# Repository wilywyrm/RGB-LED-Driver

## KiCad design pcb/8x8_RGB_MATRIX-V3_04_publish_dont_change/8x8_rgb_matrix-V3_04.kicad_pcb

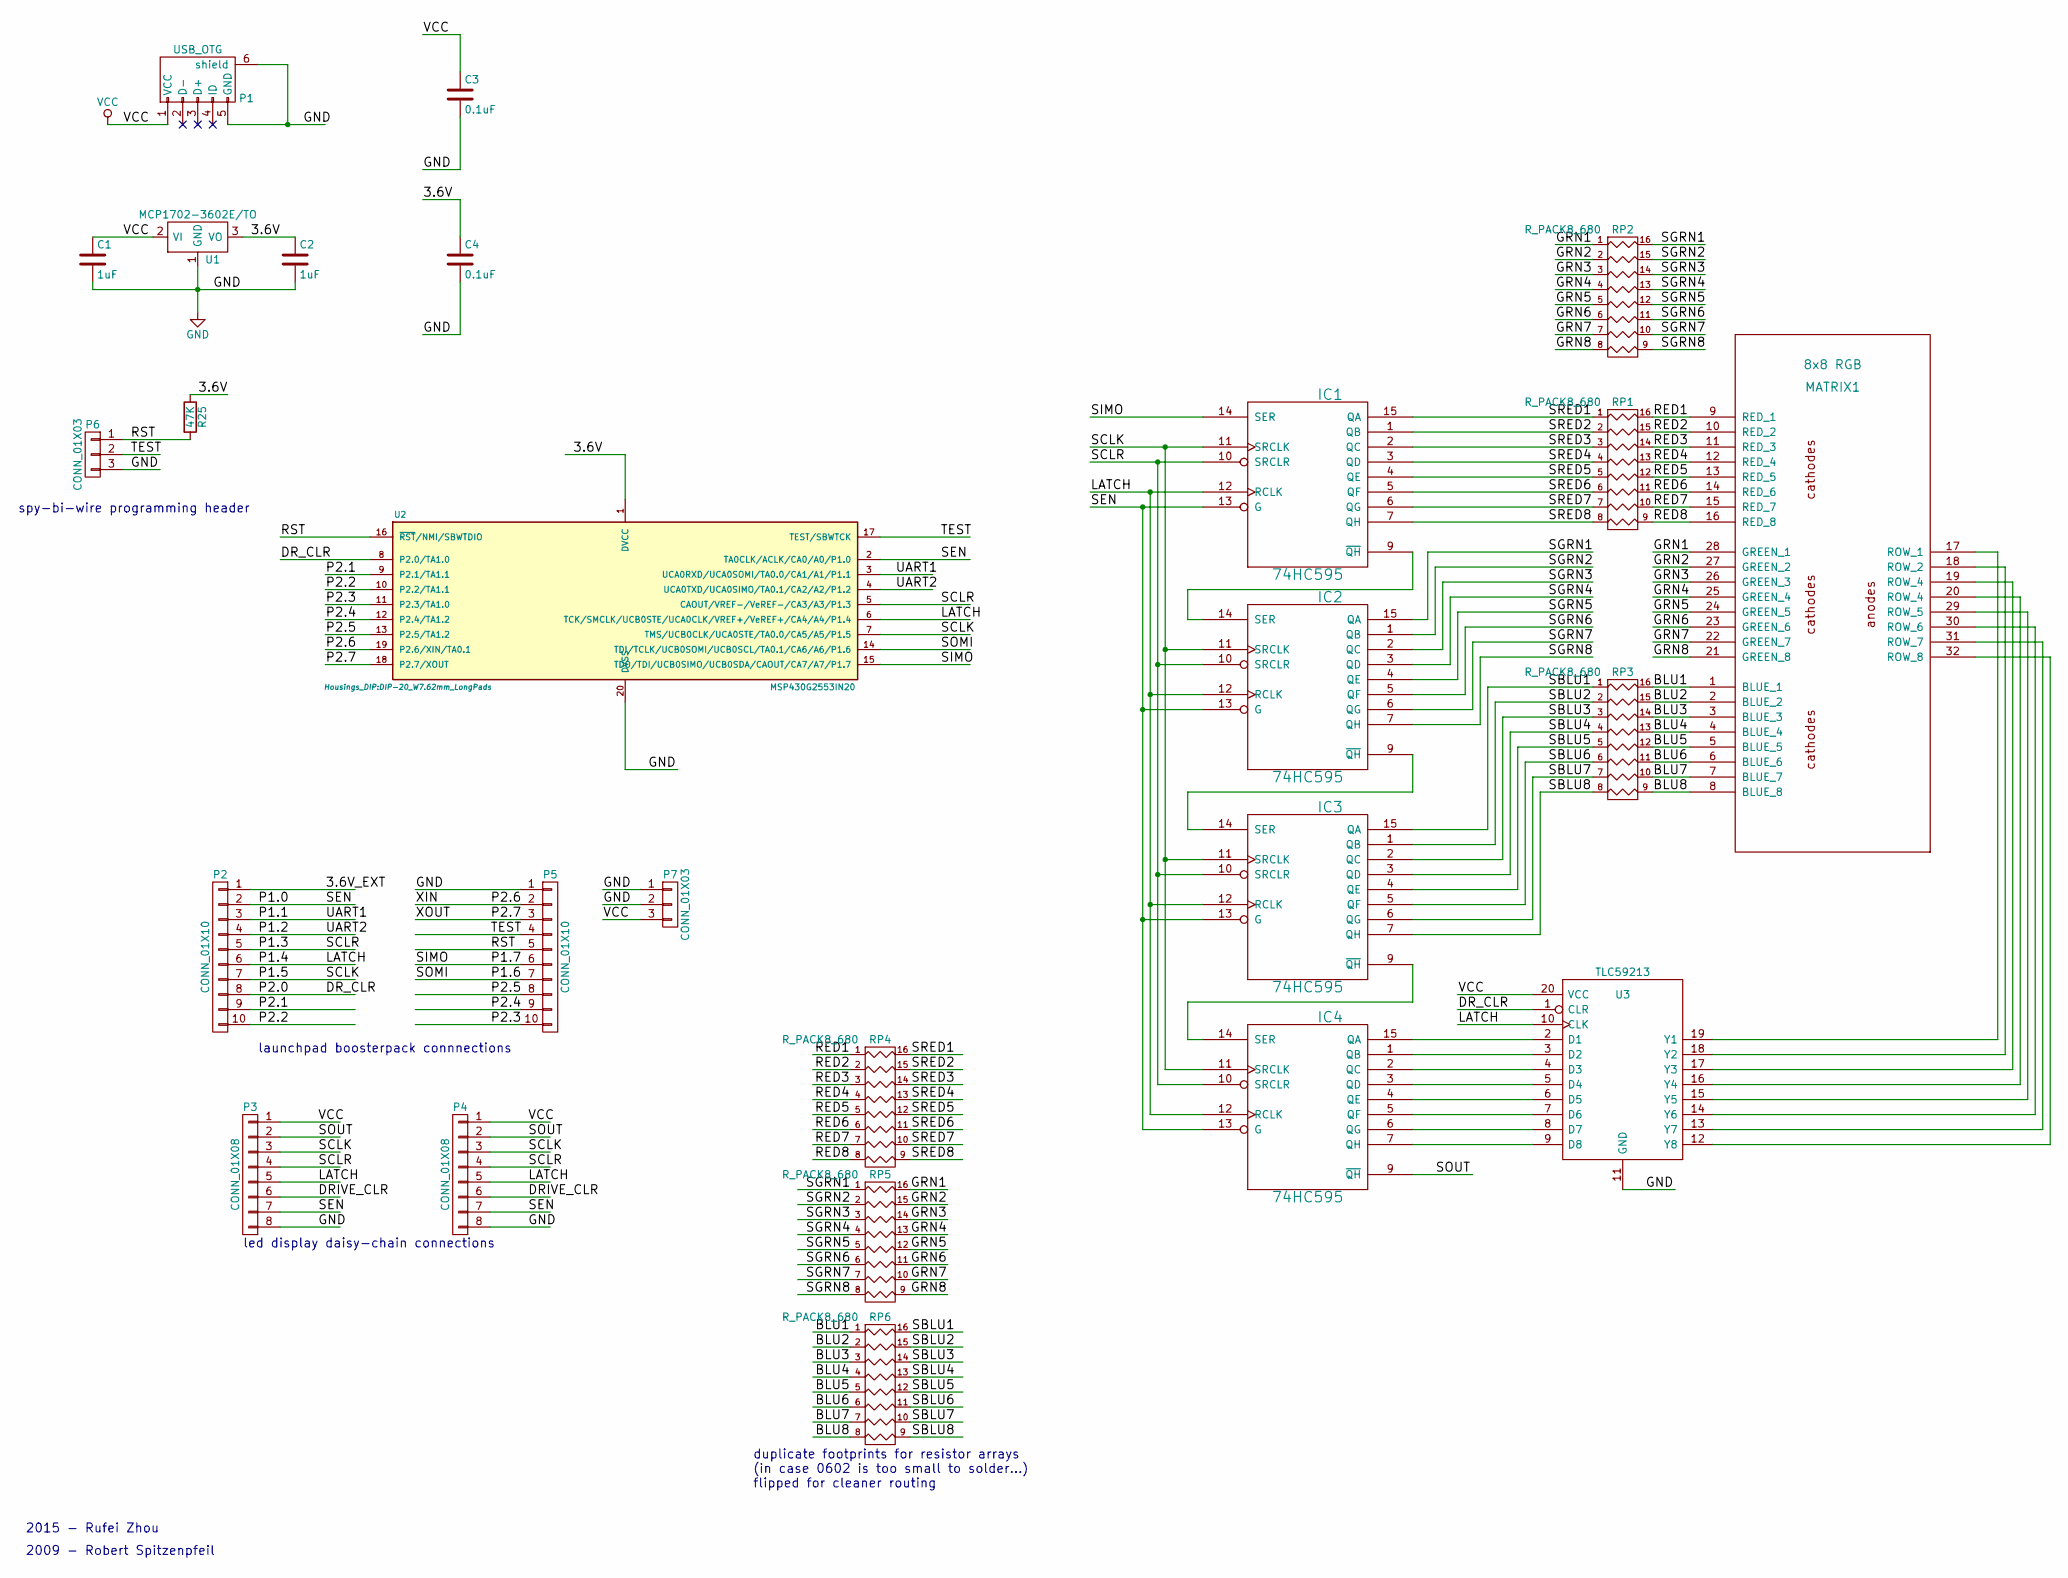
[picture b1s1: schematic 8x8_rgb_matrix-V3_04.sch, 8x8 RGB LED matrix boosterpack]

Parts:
C1, C2: 1uF; C_Disc_D3_P2.5
C3, C4: 0.1uF; C_Disc_D3_P2.5
IC1, IC2, IC3, IC4: 74HC595; SOIC-16_3.9x9.9mm_Pitch1.27mm
MATRIX1: 8x8 RGB; MADW__LEDSEE_8x8_RGB
P1: USB_OTG; USB_Micro-B_FCI
P2, P5: CONN_01X10; Pin_Header_Straight_1x10
P3: CONN_01X08; Pin_Header_Angled_1x08
P4: CONN_01X08; Pin_Header_Straight_1x08
P6, P7: CONN_01X03; Pin_Header_Straight_1x03
R25: 47K; R3
RP1, RP2, RP3: R_PACK8_680; R_Array_Convex_8x0602
RP4, RP5, RP6: R_PACK8_680; R_Array_Convex_8_2406
U1: MCP1702-3602E/TO; TO-92_Inline_Narrow_Oval
U2: MSP430G2553IN20; DIP-20_W7.62mm_LongPads
U3: TLC59213; DIP-20_W7.62mm_LongPads

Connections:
/3.6V: C2.1, C4.1, R25.1, U1.3 (VO), U2.1 (DVCC)
/3.6V_EXT: P2.1
/BLU1: MATRIX1.1 (BLUE_1), RP3.16 (R1), RP6.1; also elsewhere on the board
/BLU2: MATRIX1.2 (BLUE_2), RP3.15 (R2), RP6.2; also elsewhere on the board
/BLU3: MATRIX1.3 (BLUE_3), RP3.14 (R3), RP6.3; also elsewhere on the board
/BLU4: MATRIX1.4 (BLUE_4), RP3.13 (R4), RP6.4; also elsewhere on the board
/BLU5: MATRIX1.5 (BLUE_5), RP3.12 (R5), RP6.5; also elsewhere on the board
/BLU6: MATRIX1.6 (BLUE_6), RP3.11 (R6), RP6.6; also elsewhere on the board
/BLU7: MATRIX1.7 (BLUE_7), RP3.10 (R7), RP6.7; also elsewhere on the board
/BLU8: MATRIX1.8 (BLUE_8), RP3.9 (R8), RP6.8; also elsewhere on the board
/DRIVE_CLR: P3.6, P4.6
/DR_CLR: P2.8, U2.8 (P2.0/TA1.0), U3.1 (CLR)
/GRN1: MATRIX1.28 (GREEN_1), RP2.1, RP5.16 (R1); also elsewhere on the board
/GRN2: MATRIX1.27 (GREEN_2), RP2.2, RP5.15 (R2); also elsewhere on the board
/GRN3: MATRIX1.26 (GREEN_3), RP2.3, RP5.14 (R3); also elsewhere on the board
/GRN4: MATRIX1.25 (GREEN_4), RP2.4, RP5.13 (R4); also elsewhere on the board
/GRN5: MATRIX1.24 (GREEN_5), RP2.5, RP5.12 (R5); also elsewhere on the board
/GRN6: MATRIX1.23 (GREEN_6), RP2.6, RP5.11 (R6); also elsewhere on the board
/GRN7: MATRIX1.22 (GREEN_7), RP2.7, RP5.10 (R7); also elsewhere on the board
/GRN8: MATRIX1.21 (GREEN_8), RP2.8, RP5.9 (R8); also elsewhere on the board
/LATCH: IC1.12 (RCLK), IC2.12 (RCLK), IC3.12 (RCLK), IC4.12 (RCLK), P2.6, P3.5, P4.5, U2.6 (TCK/SMCLK/UCB0STE/UCA0CLK/VREF+/VeREF+/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), U3.10 (CLK)
/P1.0: IC1.13 (G), IC2.13 (G), IC3.13 (G), IC4.13 (G), P2.2, P3.7, P4.7, U2.2 (TA0CLK/ACLK/CA0/A0/P1.0)
/P1.1: P2.3, U2.3 (UCA0RXD/UCA0SOMI/TA0.0/CA1/A1/P1.1)
/P1.2: P2.4, U2.4 (UCA0TXD/UCA0SIMO/TA0.1/CA2/A2/P1.2)
/P1.3: IC1.10 (SRCLR), IC2.10 (SRCLR), IC3.10 (SRCLR), IC4.10 (SRCLR), P2.5, P3.4, P4.4, U2.5 (CAOUT/VREF-/VeREF-/CA3/A3/P1.3)
/P1.5: IC1.11 (SRCLK), IC2.11 (SRCLK), IC3.11 (SRCLK), IC4.11 (SRCLK), P2.7, P3.3, P4.3, U2.7 (TMS/UCB0CLK/UCA0STE/TA0.0/CA5/A5/P1.5)
/P1.6: P5.7, U2.14 (TDI/TCLK/UCB0SOMI/UCB0SCL/TA0.1/CA6/A6/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)
/P1.7: IC1.14 (SER), P5.6, U2.15 (TDO/TDI/UCB0SIMO/UCB0SDA/CAOUT/CA7/A7/P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)
/P2.1: P2.9, U2.9 (P2.1/TA1.1)
/P2.2: P2.10, U2.10 (P2.2/TA1.1)
/P2.3: P5.10, U2.11 (P2.3/TA1.0)
/P2.4: P5.9, U2.12 (P2.4/TA1.2)
/P2.5: P5.8, U2.13 (P2.5/TA1.2)
/P2.6: P5.2, U2.19 (P2.6/XIN/TA0.1)
/P2.7: P5.3, U2.18 (P2.7/XOUT)
/RED1: MATRIX1.9 (RED_1), RP1.16 (R1), RP4.1; also elsewhere on the board
/RED2: MATRIX1.10 (RED_2), RP1.15 (R2), RP4.2; also elsewhere on the board
/RED3: MATRIX1.11 (RED_3), RP1.14 (R3), RP4.3; also elsewhere on the board
/RED4: MATRIX1.12 (RED_4), RP1.13 (R4), RP4.4; also elsewhere on the board
/RED5: MATRIX1.13 (RED_5), RP1.12 (R5), RP4.5; also elsewhere on the board
/RED6: MATRIX1.14 (RED_6), RP1.11 (R6), RP4.6; also elsewhere on the board
/RED7: MATRIX1.15 (RED_7), RP1.10 (R7), RP4.7; also elsewhere on the board
/RED8: MATRIX1.16 (RED_8), RP1.9 (R8), RP4.8; also elsewhere on the board
/RST: P5.5, P6.1, R25.2, U2.16 (~RST~/NMI/SBWTDIO)
/SBLU1: IC3.15 (QA), RP3.1, RP6.16 (R1)
/SBLU2: IC3.1 (QB), RP3.2, RP6.15 (R2)
/SBLU3: IC3.2 (QC), RP3.3, RP6.14 (R3)
/SBLU4: IC3.3 (QD), RP3.4, RP6.13 (R4)
/SBLU5: IC3.4 (QE), RP3.5, RP6.12 (R5)
/SBLU6: IC3.5 (QF), RP3.6, RP6.11 (R6)
/SBLU7: IC3.6 (QG), RP3.7, RP6.10 (R7)
/SBLU8: IC3.7 (QH), RP3.8, RP6.9 (R8)
/SGRN1: IC2.15 (QA), RP2.16 (R1), RP5.1
/SGRN2: IC2.1 (QB), RP2.15 (R2), RP5.2
/SGRN3: IC2.2 (QC), RP2.14 (R3), RP5.3
/SGRN4: IC2.3 (QD), RP2.13 (R4), RP5.4
/SGRN5: IC2.4 (QE), RP2.12 (R5), RP5.5
/SGRN6: IC2.5 (QF), RP2.11 (R6), RP5.6
/SGRN7: IC2.6 (QG), RP2.10 (R7), RP5.7
/SGRN8: IC2.7 (QH), RP2.9 (R8), RP5.8
/SOUT: IC4.9 (~QH), P3.2, P4.2
/SRED1: IC1.15 (QA), RP1.1, RP4.16 (R1)
/SRED2: IC1.1 (QB), RP1.2, RP4.15 (R2)
/SRED3: IC1.2 (QC), RP1.3, RP4.14 (R3)
/SRED4: IC1.3 (QD), RP1.4, RP4.13 (R4)
/SRED5: IC1.4 (QE), RP1.5, RP4.12 (R5)
/SRED6: IC1.5 (QF), RP1.6, RP4.11 (R6)
/SRED7: IC1.6 (QG), RP1.7, RP4.10 (R7)
/SRED8: IC1.7 (QH), RP1.8, RP4.9 (R8)
/TEST: P5.4, P6.2, U2.17 (TEST/SBWTCK)
GND: C1.2, C2.2, C3.2, C4.2, IC1.8 (GND), IC2.8 (GND), IC3.8 (GND), IC4.8 (GND), P1.5 (GND), P1.6 (shield), P3.8, P4.8, P5.1, P6.3, P7.1, P7.2, U1.1 (GND), U2.20 (DVSS), U3.11 (GND)
unnamed: IC1.9 (~QH), IC2.14 (SER)
unnamed: IC2.9 (~QH), IC3.14 (SER)
unnamed: IC3.9 (~QH), IC4.14 (SER)
unnamed: IC4.1 (QB), U3.3 (D2)
unnamed: IC4.2 (QC), U3.4 (D3)
unnamed: IC4.3 (QD), U3.5 (D4)
unnamed: IC4.4 (QE), U3.6 (D5)
unnamed: IC4.5 (QF), U3.7 (D6)
unnamed: IC4.6 (QG), U3.8 (D7)
unnamed: IC4.7 (QH), U3.9 (D8)
unnamed: IC4.15 (QA), U3.2 (D1)
unnamed 82: MATRIX1.17 (ROW_1), U3.19 (Y1); also elsewhere on the board
unnamed 83: MATRIX1.18 (ROW_2), U3.18 (Y2); also elsewhere on the board
unnamed 84: MATRIX1.19 (ROW_4), U3.17 (Y3); also elsewhere on the board
unnamed 85: MATRIX1.20 (ROW_4), U3.16 (Y4); also elsewhere on the board
unnamed 86: MATRIX1.29 (ROW_5), U3.15 (Y5); also elsewhere on the board
unnamed 87: MATRIX1.30 (ROW_6), U3.14 (Y6); also elsewhere on the board
unnamed 88: MATRIX1.31 (ROW_7), U3.13 (Y7); also elsewhere on the board
unnamed 89: MATRIX1.32 (ROW_8), U3.12 (Y8); also elsewhere on the board
VCC: C1.1, C3.1, IC1.16 (VCC), IC2.16 (VCC), IC3.16 (VCC), IC4.16 (VCC), P1.1 (VCC), P3.1, P4.1, P7.3, U1.2 (VI), U3.20 (VCC)

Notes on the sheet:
2009 - Robert Spitzenpfeil
launchpad boosterpack connnections
spy-bi-wire programming header
led display daisy-chain connections
2015 - Rufei Zhou
duplicate footprints for resistor arrays (in case 0602 is too small to solder...) flipped for cleaner routing

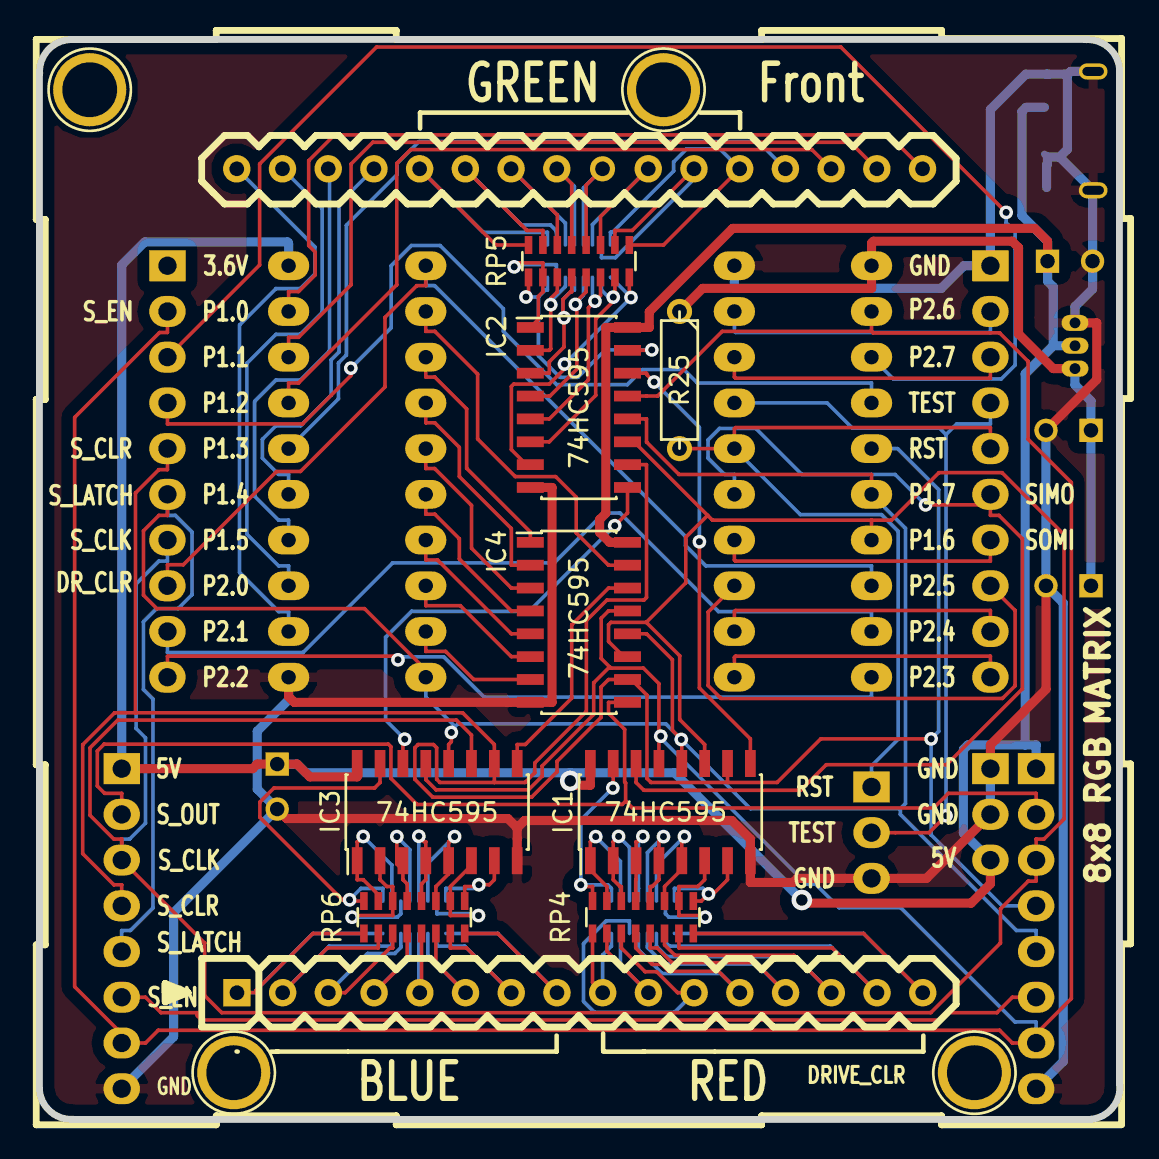
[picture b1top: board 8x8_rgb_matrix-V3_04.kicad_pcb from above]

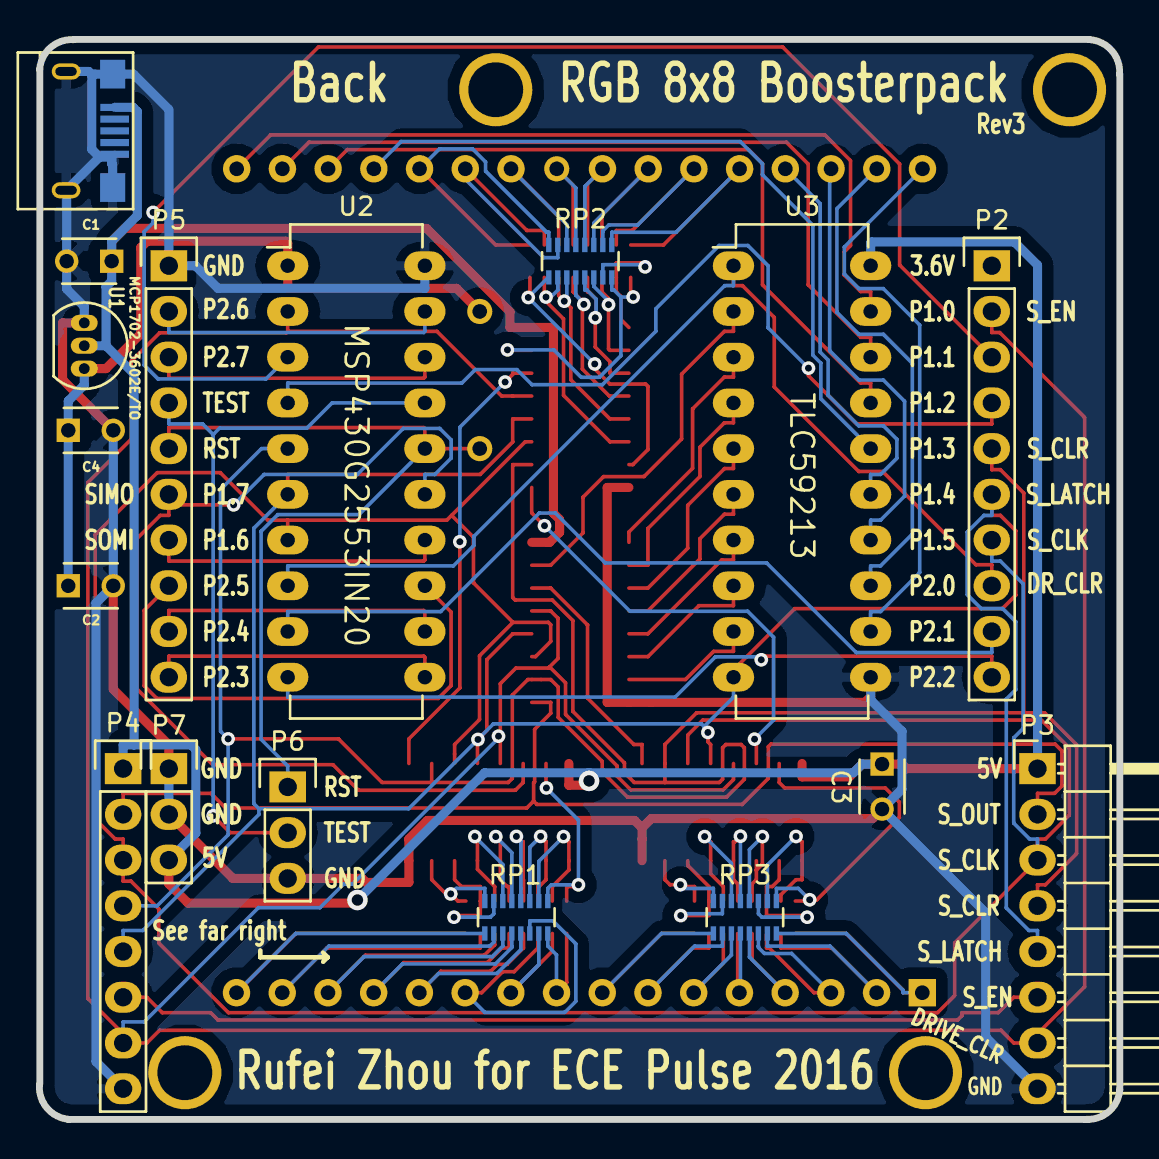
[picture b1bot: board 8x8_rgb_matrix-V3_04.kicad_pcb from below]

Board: 2 copper layers, 60.0 x 60.0 mm, 30 parts (17 on the bottom side), 90 nets.

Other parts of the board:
M1, M2, M3, M4: 1pin
MATRIX: 8x8 RGB; MADW__LEDSEE_8x8_RGB

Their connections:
/BLU1: MATRIX.1; also elsewhere on the board
/BLU2: MATRIX.2; also elsewhere on the board
/BLU3: MATRIX.3; also elsewhere on the board
/BLU4: MATRIX.4; also elsewhere on the board
/BLU5: MATRIX.5; also elsewhere on the board
/BLU6: MATRIX.6; also elsewhere on the board
/BLU7: MATRIX.7; also elsewhere on the board
/BLU8: MATRIX.8; also elsewhere on the board
/GRN1: MATRIX.28; also elsewhere on the board
/GRN2: MATRIX.27; also elsewhere on the board
/GRN3: MATRIX.26; also elsewhere on the board
/GRN4: MATRIX.25; also elsewhere on the board
/GRN5: MATRIX.24; also elsewhere on the board
/GRN6: MATRIX.23; also elsewhere on the board
/GRN7: MATRIX.22; also elsewhere on the board
/GRN8: MATRIX.21; also elsewhere on the board
/RED1: MATRIX.9; also elsewhere on the board
/RED2: MATRIX.10; also elsewhere on the board
/RED3: MATRIX.11; also elsewhere on the board
/RED4: MATRIX.12; also elsewhere on the board
/RED5: MATRIX.13; also elsewhere on the board
/RED6: MATRIX.14; also elsewhere on the board
/RED7: MATRIX.15; also elsewhere on the board
/RED8: MATRIX.16; also elsewhere on the board
unnamed 82: MATRIX.17; also elsewhere on the board
unnamed 83: MATRIX.18; also elsewhere on the board
unnamed 84: MATRIX.19; also elsewhere on the board
unnamed 85: MATRIX.20; also elsewhere on the board
unnamed 86: MATRIX.29; also elsewhere on the board
unnamed 87: MATRIX.30; also elsewhere on the board
unnamed 88: MATRIX.31; also elsewhere on the board
unnamed 89: MATRIX.32; also elsewhere on the board

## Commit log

2016-01-27 :lollipop: Added .gitattributes
2016-12-26 forgot to commit solution code only to find out nearly an entire year later
    whoops
    this is also untested cause i dont have the board with me during winter
    break
